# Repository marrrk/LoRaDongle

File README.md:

# LoRaDongle

LoRaDongle is a custom PCB that merges Risc-V with LoRa in a USB Dongle form factor. This repository contains all the project files required to build, utilise and modify the project. Documentation can be read from the site: [https://marrrk.github.io/LoRaDongle/](https://marrrk.github.io/LoRaDongle/)

## Cloning the repository

```bash
git clone --recurse-submodules https://github.com/marrrk/LoRaDongle.git
```

## Directory Structure

- PCB/ -  Contains the Kicad project files, schematics, gerbers, BOM and other PCB related files
- SOC/ - The python scripts that generate, build and load the Risc-V SoC onto the PCB
- firmware/ -  SUpporting firmware that runs on the SoC
- docs/ - Source files for the documentation website

**License** Licensed under [CERN-OHL-P v2](https://cern-ohl.web.cern.ch/) permissive variant or later.

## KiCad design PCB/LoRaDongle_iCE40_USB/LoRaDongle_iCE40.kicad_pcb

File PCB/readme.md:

# Overview
In order to open the Kicad project, open kicad and open the project file `LoRaDongle_iCE40.kicad_pro`. The schematic has been implemented with hierarchal sheets which allows the different submodules to be their own separate schematic. There are five total schematics for each module;
1. LoRaDongle_ice40.kicad_sch
2. power_management.kicad_sch
3. USB_Interface.kicad_sch
4. ice40up5k_sircuit.kicad_sch
5. sx1261_circuitry.kicad_sch

The other files and directories of relevance are:
- libraries/ - kicad symbols and footprints of specific components used
- manufacturing/  - gerbers, assembly files and images for manufacturing
- pdf_schematic/ - pdfs of the schematics of all versions
- silksceen/ - images that are converted into silkscreen footprints

# Contents of the Schematics
## LoRaDongle_ice40
The root schematic that is at the top of the heirarchy. Contains the connecting signals between various subsystems and other components such as the USB connector.

## power_management.kicad_sch
Contains the board's regulator. Steps down 5V to 3.3V and 1.2V.

## USB_Interface.kicad_sch
Houses the FTDI FT2232HL IC that converts the USB protocol into SPI for the FPGA configuration and UART for communicating with the SoC.

## ice40up5k_circuit.kicad_sch
This schematic holds the FPGA banks and related circuitry. This includes the SPI Flash, the oscillator, gas sensor and a header of all unused pins.

## sx1261_circuitry.kicad_sch
This is the RF section of the schematic. It contains the LoRa chip used (SX1261) and the supporting circuitry.

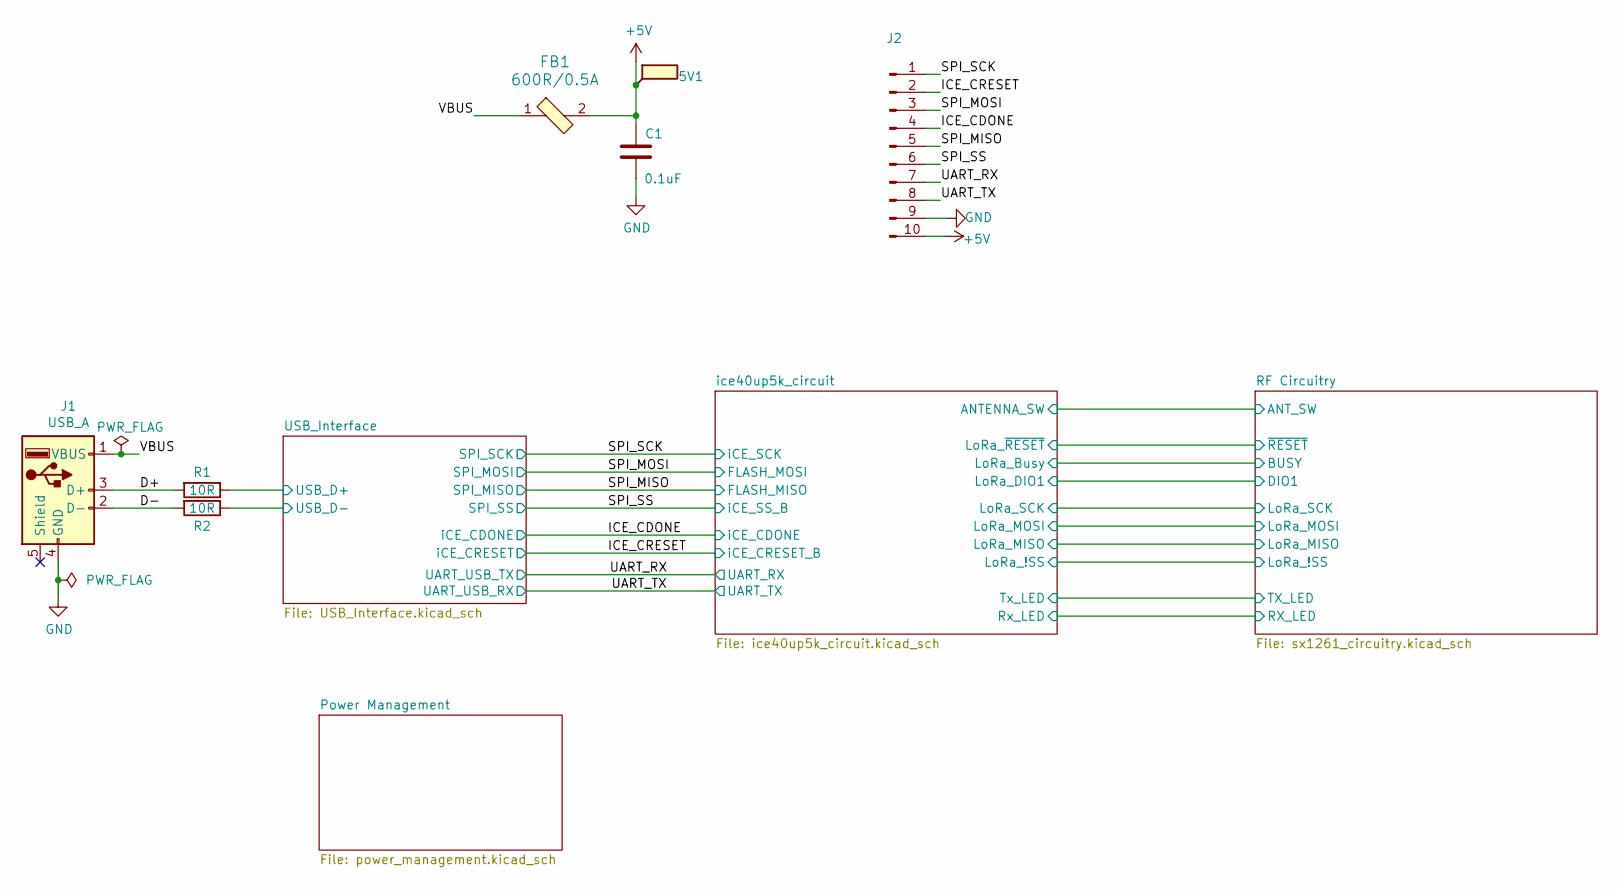
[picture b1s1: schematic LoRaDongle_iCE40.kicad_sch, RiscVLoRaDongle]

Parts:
5V1: 5V; TestPoint_Pad_D2.5mm
C1: 0.1uF; C_0402_1005Metric_Pad0.74x0.62mm_HandSolder; Part Number GCM155R71C104KA55J
FB1: 600R/0.5A; 0603; MPN BLM18AG601SN1D; Digi-Key_PN 490-1014-1-ND
J1: USB_A; USB_A_CNCTech_1001-011-01101_Horizontal; Manufacturer Part Number USB-AP-S-RA-SMT
J2: Conn_01x10_Male; PinHeader_2x05_P2.54mm_Vertical
R1, R2: 10R; R_0402_1005Metric_Pad0.72x0.64mm_HandSolder; Manufacturer Part Number RMCF0402FT10R0

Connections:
+5V: 5V1.1, C1.2, FB1.2, J2.10; also elsewhere on the board
/D+: J1.3 (D+), R1.2
/D-: J1.2 (D-), R2.2
/ICE_CDONE: J2.4; also elsewhere on the board
/ICE_CRESET: J2.2; also elsewhere on the board
/SPI_MISO: J2.5; also elsewhere on the board
/SPI_MOSI: J2.3; also elsewhere on the board
/SPI_SCK: J2.1; also elsewhere on the board
/SPI_SS: J2.6; also elsewhere on the board
/UART_RX: J2.7; also elsewhere on the board
/UART_TX: J2.8; also elsewhere on the board
/USB_Interface/USB_D+: R1.1; also elsewhere on the board
/USB_Interface/USB_D-: R2.1; also elsewhere on the board
/VBUS: FB1.1, J1.1 (VBUS)
GND: C1.1, J1.4 (GND), J2.9; also elsewhere on the board

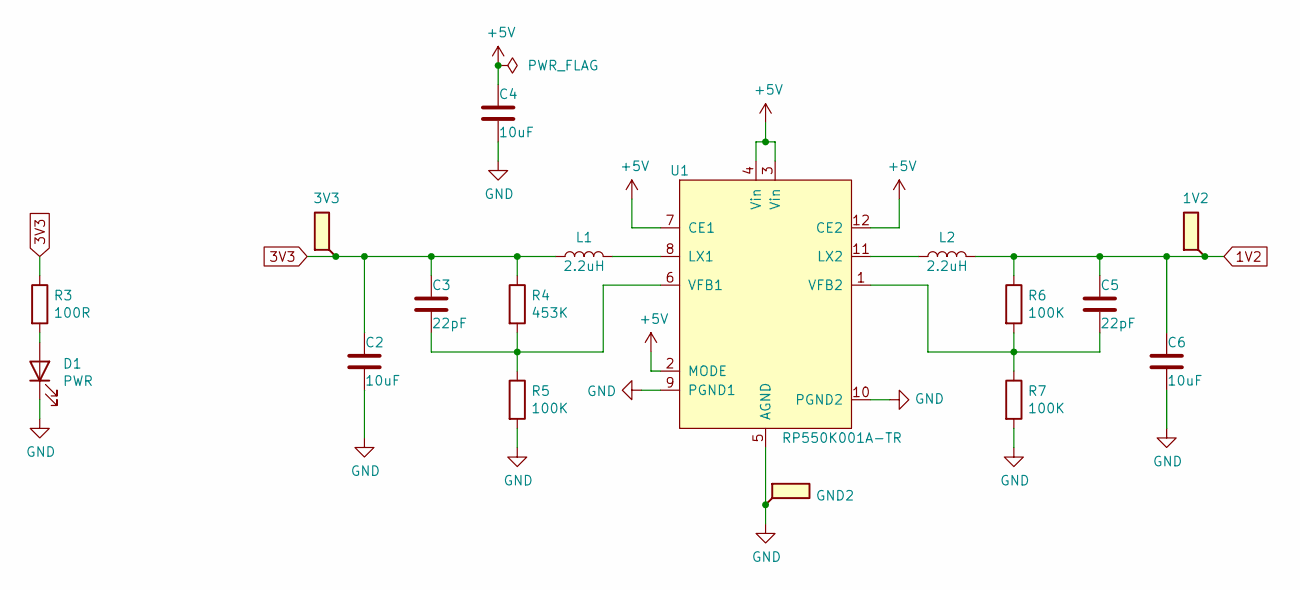
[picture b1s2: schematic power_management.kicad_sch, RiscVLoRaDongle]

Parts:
1V2: 1.2V; TestPoint_Pad_D2.5mm
3V3: 3.3V; TestPoint_Pad_D2.5mm
C2, C4, C6: 10uF; C_0603_1608Metric_Pad1.08x0.95mm_HandSolder; Part Number GRM188R61E106KA73J
C3, C5: 22pF; C_0402_1005Metric_Pad0.74x0.62mm_HandSolder; Part Number GRM1555C1H220FA01D
D1: PWR; LED_0603_1608Metric; Manufacturer Part Number LTST-C191KRKT
GND2: GND; TestPoint_Pad_D2.5mm
L1, L2: 2.2uH; L_0603_1608Metric_Pad1.05x0.95mm_HandSolder; Part Number MCHK1608T2R2MKN
R3: 100R; R_0402_1005Metric_Pad0.72x0.64mm_HandSolder; Manufacturer Part Number RMCF0402FT100R
R4: 453K; R_0402_1005Metric_Pad0.72x0.64mm_HandSolder; Manufacturer Part Number RMCF0402FT453K
R5, R6, R7: 100K; R_0402_1005Metric_Pad0.72x0.64mm_HandSolder; Manufacturer Part Number RMCF0402JT100K
U1: RP550K001A-TR; SON50P270X300X60-13N; Manufacturer Part Number RP550K001A-TR

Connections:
1V2: 1V2.1, C5.2, C6.2, L2.2, R6.1; also elsewhere on the board
3V3: 3V3.1, C2.2, C3.2, L1.1, R3.1, R4.1; also elsewhere on the board
+5V: C4.2, U1.2 (MODE), U1.3 (Vin), U1.4 (Vin), U1.7 (CE1), U1.12 (CE2); also elsewhere on the board
GND: C2.1, C4.1, C6.1, D1.1 (K), GND2.1, R5.2, R7.2, U1.5 (AGND), U1.9 (PGND1), U1.10 (PGND2); also elsewhere on the board
unnamed: C3.1, R4.2, R5.1, U1.6 (VFB1)
unnamed: C5.1, R6.2, R7.1, U1.1 (VFB2)
unnamed: D1.2 (A), R3.2
unnamed: L1.2, U1.8 (LX1)
unnamed: L2.1, U1.11 (LX2)

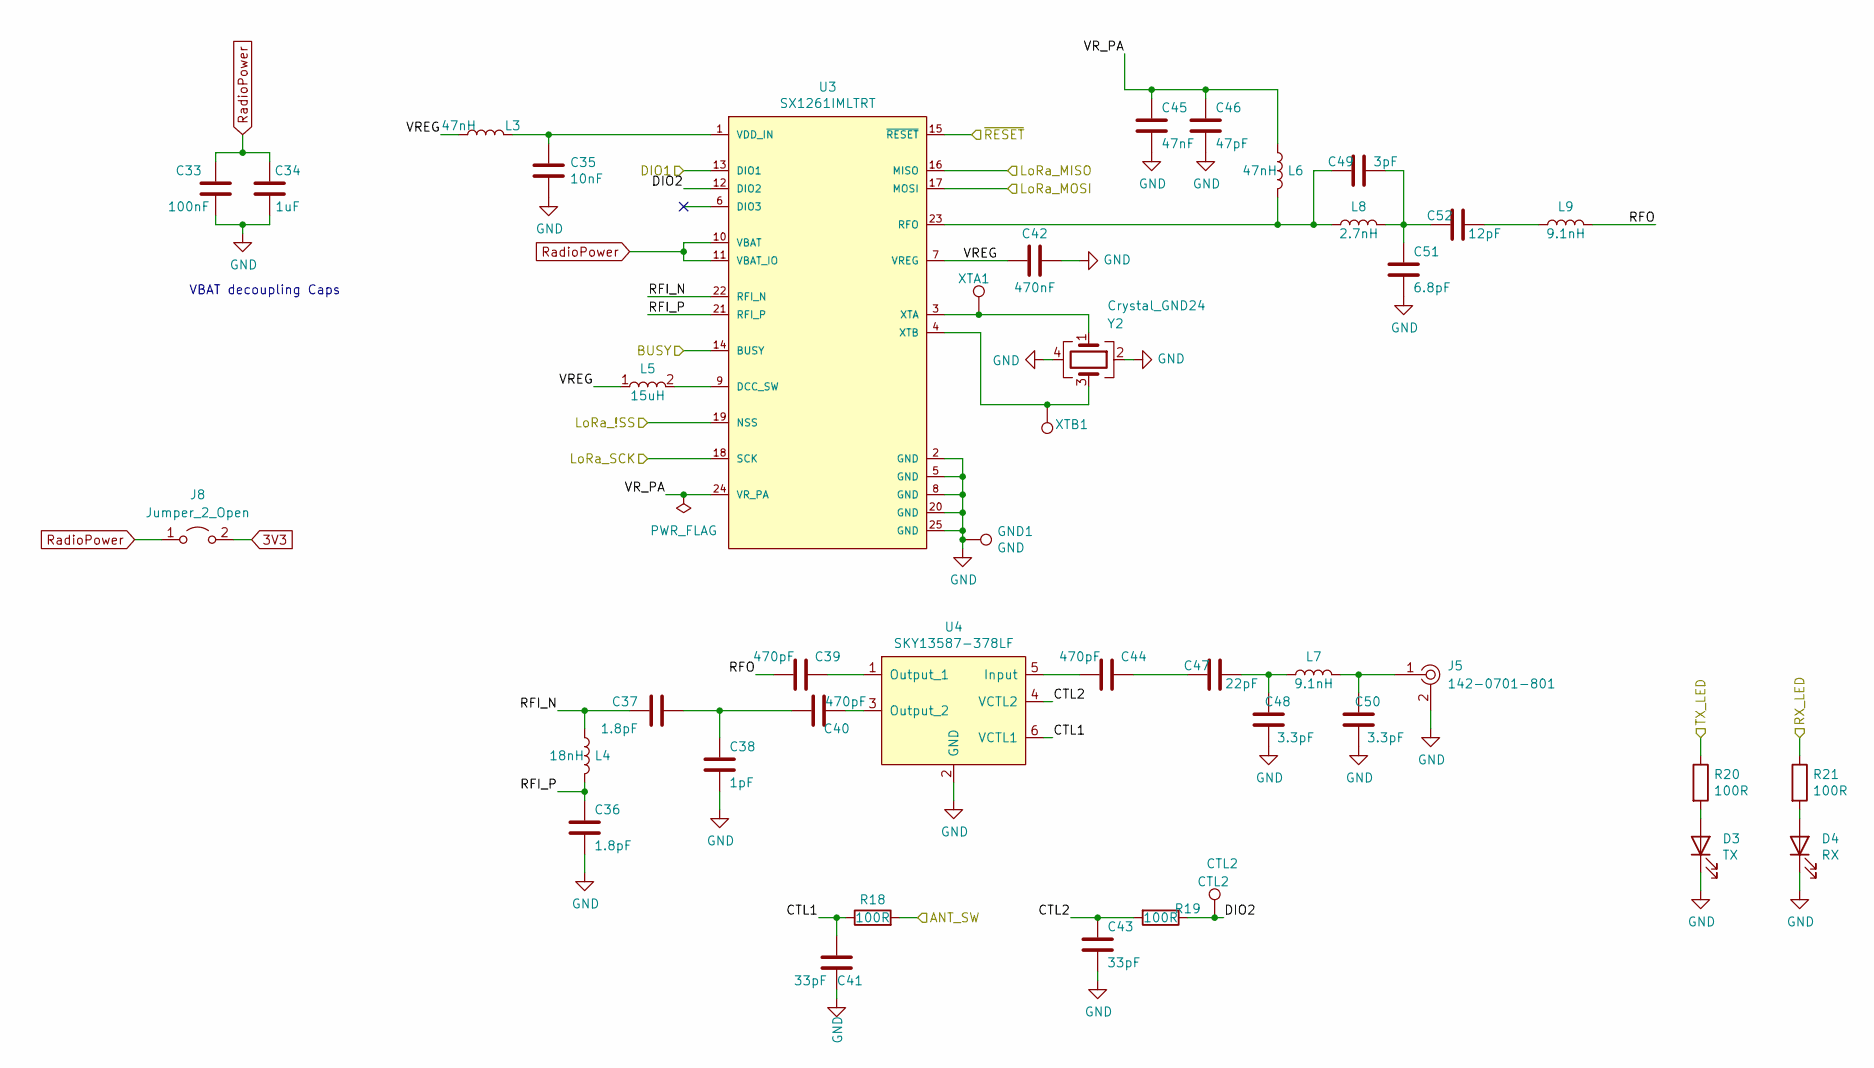
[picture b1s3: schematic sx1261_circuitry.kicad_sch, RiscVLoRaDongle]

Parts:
C33: 100nF; C_0402_1005Metric_Pad0.74x0.62mm_HandSolder; Part Number GRM155R71C104KA88D
C34: 1uF; C_0402_1005Metric_Pad0.74x0.62mm_HandSolder; Manufacturer Part Number GRM155R70J105MA12D
C35: 10nF; C_0402_1005Metric_Pad0.74x0.62mm_HandSolder; Part Number GRM155R71H103KA88J
C36, C37: 1.8pF; C_0402_1005Metric_Pad0.74x0.62mm_HandSolder; part Number GRM1555C1H1R8WA01D
C38: 1pF; C_0402_1005Metric_Pad0.74x0.62mm_HandSolder; part Number GRM1555C1H1R0BA01D
C39, C40, C44: 470pF; C_0402_1005Metric_Pad0.74x0.62mm_HandSolder; Part Number GRM1555C1H471JA01D
C41, C43: 33pF; C_0402_1005Metric_Pad0.74x0.62mm_HandSolder; Part Number CGA2B2C0G1H330J050BA
C42: 470nF; C_0402_1005Metric_Pad0.74x0.62mm_HandSolder; Part Number GRM155R61A474KE15D
C45: 47nF; C_0402_1005Metric_Pad0.74x0.62mm_HandSolder; Part Number GRM155R71C473KA01J
C46: 47pF; C_0402_1005Metric_Pad0.74x0.62mm_HandSolder; Part Number GRM1555C1H470JA01D
C47: 22pF; C_0402_1005Metric_Pad0.74x0.62mm_HandSolder; Part Number GRM1555C1H220JA01D
C48, C50: 3.3pF; C_0402_1005Metric_Pad0.74x0.62mm_HandSolder; Part Number GJM1555C1H3R3DB01D
C49: 3pF; C_0402_1005Metric_Pad0.74x0.62mm_HandSolder; Part Number GRM1555C1H3R0BA01J
C51: 6.8pF; C_0402_1005Metric_Pad0.74x0.62mm_HandSolder; Part Number GRM1555C1H6R8BA01D
C52: 12pF; C_0402_1005Metric_Pad0.74x0.62mm_HandSolder; Part Number GRM1555C1H120JA01J
CTL2: CTL2; TestPoint_Pad_D2.5mm
D3: TX; LED_0603_1608Metric_Pad1.05x0.95mm_HandSolder; Manufacturer Part Number XZVG53W-8
D4: RX; LED_0603_1608Metric_Pad1.05x0.95mm_HandSolder; Manufacturer Part Number XZVG53W-8
GND1: GND; TestPoint_Pad_D2.5mm
J5: 142-0701-801; RF_SMA_BoardEdge_142-0701-801; MPN 142-0701-801; Digi-Key_PN J502-ND
J8: Jumper_2_Open; PinHeader_1x02_P2.54mm_Vertical
L3: 47nH; L_0402_1005Metric_Pad0.77x0.64mm_HandSolder; PartNumber LQW15AN47NJ00D
L4: 18nH; L_0402_1005Metric_Pad0.77x0.64mm_HandSolder; part Number LQW15AN18NH00D
L5: 15uH; VLS2016; Manufacturer_Part_Number VLS201610CX-150M-1; Mouser Part Number 810-VLS201610CX150M1
L6: 47nH; L_0402_1005Metric_Pad0.77x0.64mm_HandSolder; Part Number LQW15AN47NJ00D
L7, L9: 9.1nH; L_0402_1005Metric_Pad0.77x0.64mm_HandSolder; Part Number LQW15AN9N1H00D
L8: 2.7nH; L_0402_1005Metric_Pad0.77x0.64mm_HandSolder; Part Number LQW15AN2N7C00D
R18, R19, R20, R21: 100R; R_0402_1005Metric_Pad0.72x0.64mm_HandSolder; Manufacturer Part Number RMCF0402FT100R
U3: SX1261IMLTRT; Semtech-QFN24-0-0-0; mouser part number 947-SX1261IMLTRT; digikey description TXRX LORA SUB-GHZ 15DBM 24MLPQ
U4: SKY13587-378LF; SW_SKYA21012; Manufacturer Part Number SKY13587-378LF
XTA1: XTA; TestPoint_Pad_D2.5mm
XTB1: XTB; TestPoint_Pad_D2.5mm
Y2: Crystal_GND24; Crystal_SMD_2520-4Pin_2.5x2.0mm; Part Number ECS-320-10-36B-CKM-TR

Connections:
3V3: J8.2 (B); also elsewhere on the board
/RF Circuitry/ANT_SW: R18.2; also elsewhere on the board
/RF Circuitry/BUSY: U3.14 (BUSY); also elsewhere on the board
/RF Circuitry/CTL1: C41.2, R18.1, U4.6 (VCTL1)
/RF Circuitry/CTL2: C43.1, R19.2, U4.4 (VCTL2)
/RF Circuitry/DIO1: U3.13 (DIO1); also elsewhere on the board
/RF Circuitry/DIO2: CTL2.1, R19.1, U3.12 (DIO2)
/RF Circuitry/LoRa_!SS: U3.19 (NSS); also elsewhere on the board
/RF Circuitry/LoRa_MISO: U3.16 (MISO); also elsewhere on the board
/RF Circuitry/LoRa_MOSI: U3.17 (MOSI); also elsewhere on the board
/RF Circuitry/LoRa_SCK: U3.18 (SCK); also elsewhere on the board
/RF Circuitry/RFI_N: C37.1, L4.1, U3.22 (RFI_N)
/RF Circuitry/RFI_P: C36.1, L4.2, U3.21 (RFI_P)
/RF Circuitry/RFO: C39.1, L9.2
/RF Circuitry/RX_LED: R21.1; also elsewhere on the board
/RF Circuitry/TX_LED: R20.1; also elsewhere on the board
/RF Circuitry/VREG: C42.2, L3.1, L5.1, U3.7 (VREG)
/RF Circuitry/VR_PA: C45.1, C46.1, L6.1, U3.24 (VR_PA)
/RF Circuitry/~RESET: U3.15 (~RESET); also elsewhere on the board
GND: C33.1, C34.1, C35.2, C36.2, C38.2, C41.1, C42.1, C43.2, C45.2, C46.2, C48.1, C50.1, C51.2, D3.1 (K), D4.1 (K), GND1.1, J5.2, U3.2 (GND), U3.5 (GND), U3.8 (GND), U3.20 (GND), U3.25 (GND), U4.2 (GND), Y2.2, Y2.4; also elsewhere on the board
unnamed: C35.1, L3.2, U3.1 (VDD_IN)
unnamed: C37.2, C38.1, C40.1
unnamed: C39.2, U4.1 (Output_1)
unnamed: C40.2, U4.3 (Output_2)
unnamed: C44.1, U4.5 (Input)
unnamed: C44.2, C47.2
unnamed: C47.1, C48.2, L7.1
unnamed: C49.1, C51.1, C52.2, L8.2
unnamed: C49.2, L6.2, L8.1, U3.23 (RFO)
unnamed: C50.2, J5.1, L7.2
unnamed: C52.1, L9.1
unnamed: D3.2 (A), R20.2
unnamed: D4.2 (A), R21.2
unnamed: L5.2, U3.9 (DCC_SW)
unnamed: U3.3 (XTA), XTA1.1, Y2.1
unnamed: U3.4 (XTB), XTB1.1, Y2.3
RadioPower: C33.2, C34.2, J8.1 (A), U3.10 (VBAT), U3.11 (VBAT_IO)

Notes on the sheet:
VBAT decoupling Caps

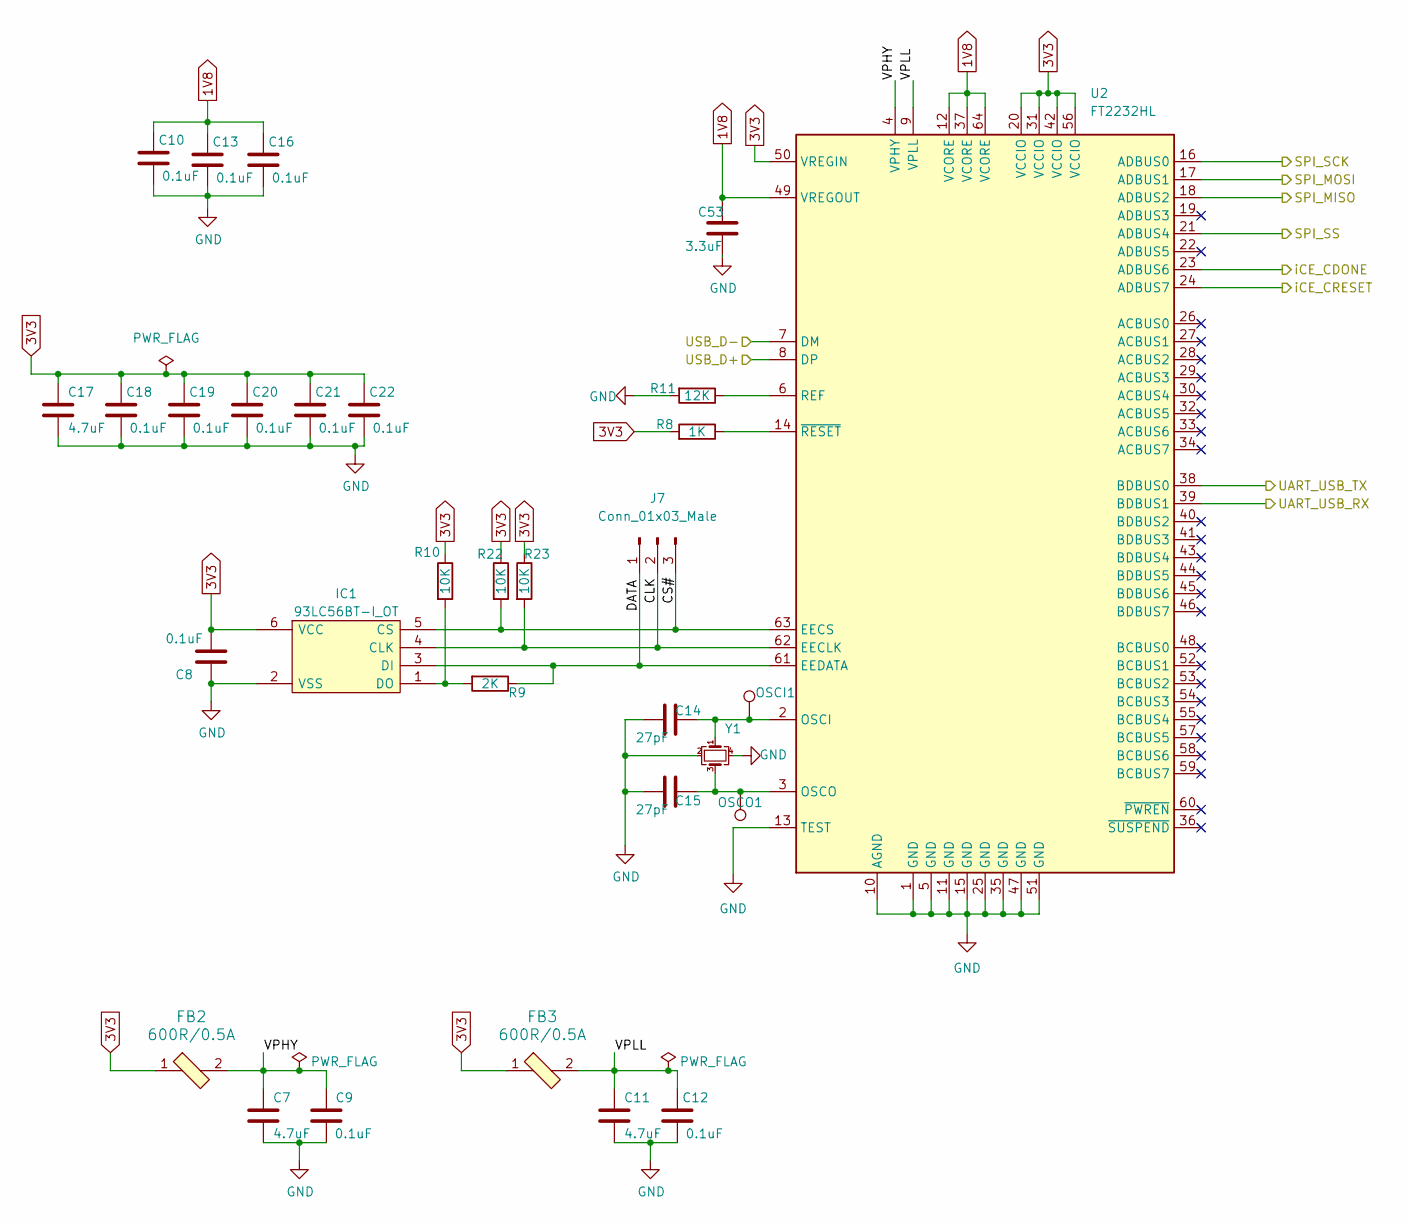
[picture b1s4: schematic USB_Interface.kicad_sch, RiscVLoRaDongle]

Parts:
C7, C11, C17: 4.7uF; C_0402_1005Metric_Pad0.74x0.62mm_HandSolder; Part Number GRM155C80J475MEAAD
C8, C9, C10, C12, C13, C16, C18, C19, C20, C21, C22: 0.1uF; C_0402_1005Metric_Pad0.74x0.62mm_HandSolder; Part Number GCM155R71C104KA55J
C14, C15: 27pF; C_0603_1608Metric_Pad1.08x0.95mm_HandSolder; Manufacturer Part Number GRM1885C1H270JA01D
C53: 3.3uF; C_0603_1608Metric_Pad1.08x0.95mm_HandSolder; Manufacturer Part Number CL10A335KP8NNNC
FB2, FB3: 600R/0.5A; 0603; MPN BLM18AG601SN1D; Digi-Key_PN 490-1014-1-ND
IC1: 93LC56BT-I_OT; SOT95P270X145-6N; Manufacturer_Part_Number 93LC56BT-I/OT; Mouser Part Number 579-93LC56BT-I/OT
J7: Conn_01x03_Male; PinHeader_1x03_P2.54mm_Vertical
OSCI1: OSCI; TestPoint_Pad_D2.5mm
OSCO1: OSCO; TestPoint_Pad_D2.5mm
R8: 1K; R_0402_1005Metric_Pad0.72x0.64mm_HandSolder; Manufacturer Part Number RMCF0402FT1K00
R9: 2K; R_0402_1005Metric_Pad0.72x0.64mm_HandSolder; Manufacturer Part Number RMCF0402FT2K00
R10, R22, R23: 10K; R_0402_1005Metric_Pad0.72x0.64mm_HandSolder; Manufacturer Part Number RMCF0402FT10K0
R11: 12K; R_0402_1005Metric_Pad0.72x0.64mm_HandSolder; Manufacturer Part Number RMCF0402FT12K0
U2: FT2232HL; LQFP-64_10x10mm_P0.5mm; Manufacturer Part Number FT2232HL
Y1: Crystal_GND24_Small; Crystal_SMD_3225-4Pin_3.2x2.5mm; Part Number ABM8-12.000MHZ-B2-T

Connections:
1V8: C10.2, C13.2, C16.2, C53.1, U2.12 (VCORE), U2.37 (VCORE), U2.49 (VREGOUT), U2.64 (VCORE)
3V3: C8.2, C17.1, C18.2, C19.2, C20.2, C21.2, C22.2, FB2.1, FB3.1, IC1.6 (VCC), R8.2, R10.1, R22.1, R23.1, U2.20 (VCCIO), U2.31 (VCCIO), U2.42 (VCCIO), U2.50 (VREGIN), U2.56 (VCCIO); also elsewhere on the board
/ICE_CDONE: U2.23 (ADBUS6); also elsewhere on the board
/ICE_CRESET: U2.24 (ADBUS7); also elsewhere on the board
/SPI_MISO: U2.18 (ADBUS2); also elsewhere on the board
/SPI_MOSI: U2.17 (ADBUS1); also elsewhere on the board
/SPI_SCK: U2.16 (ADBUS0); also elsewhere on the board
/SPI_SS: U2.21 (ADBUS4); also elsewhere on the board
/UART_RX: U2.38 (BDBUS0); also elsewhere on the board
/UART_TX: U2.39 (BDBUS1); also elsewhere on the board
/USB_Interface/CLK: IC1.4 (CLK), J7.2, R23.2, U2.62 (EECLK)
/USB_Interface/CS#: IC1.5 (CS), J7.3, R22.2, U2.63 (EECS)
/USB_Interface/DATA: IC1.3 (DI), J7.1, R9.1, U2.61 (EEDATA)
/USB_Interface/USB_D+: U2.8 (DP); also elsewhere on the board
/USB_Interface/USB_D-: U2.7 (DM); also elsewhere on the board
/USB_Interface/VPHY: C7.1, C9.2, FB2.2, U2.4 (VPHY)
/USB_Interface/VPLL: C11.1, C12.2, FB3.2, U2.9 (VPLL)
GND: C7.2, C8.1, C9.1, C10.1, C11.2, C12.1, C13.1, C14.2, C15.2, C16.1, C17.2, C18.1, C19.1, C20.1, C21.1, C22.1, C53.2, IC1.2 (VSS), R11.2, U2.1 (GND), U2.5 (GND), U2.10 (AGND), U2.11 (GND), U2.13 (TEST), U2.15 (GND), U2.25 (GND), U2.35 (GND), U2.47 (GND), U2.51 (GND), Y1.2, Y1.4; also elsewhere on the board
unnamed: C14.1, OSCI1.1, U2.2 (OSCI), Y1.1
unnamed: C15.1, OSCO1.1, U2.3 (OSCO), Y1.3
unnamed: IC1.1 (DO), R9.2, R10.2
unnamed: R8.1, U2.14 (~RESET)
unnamed: R11.1, U2.6 (REF)

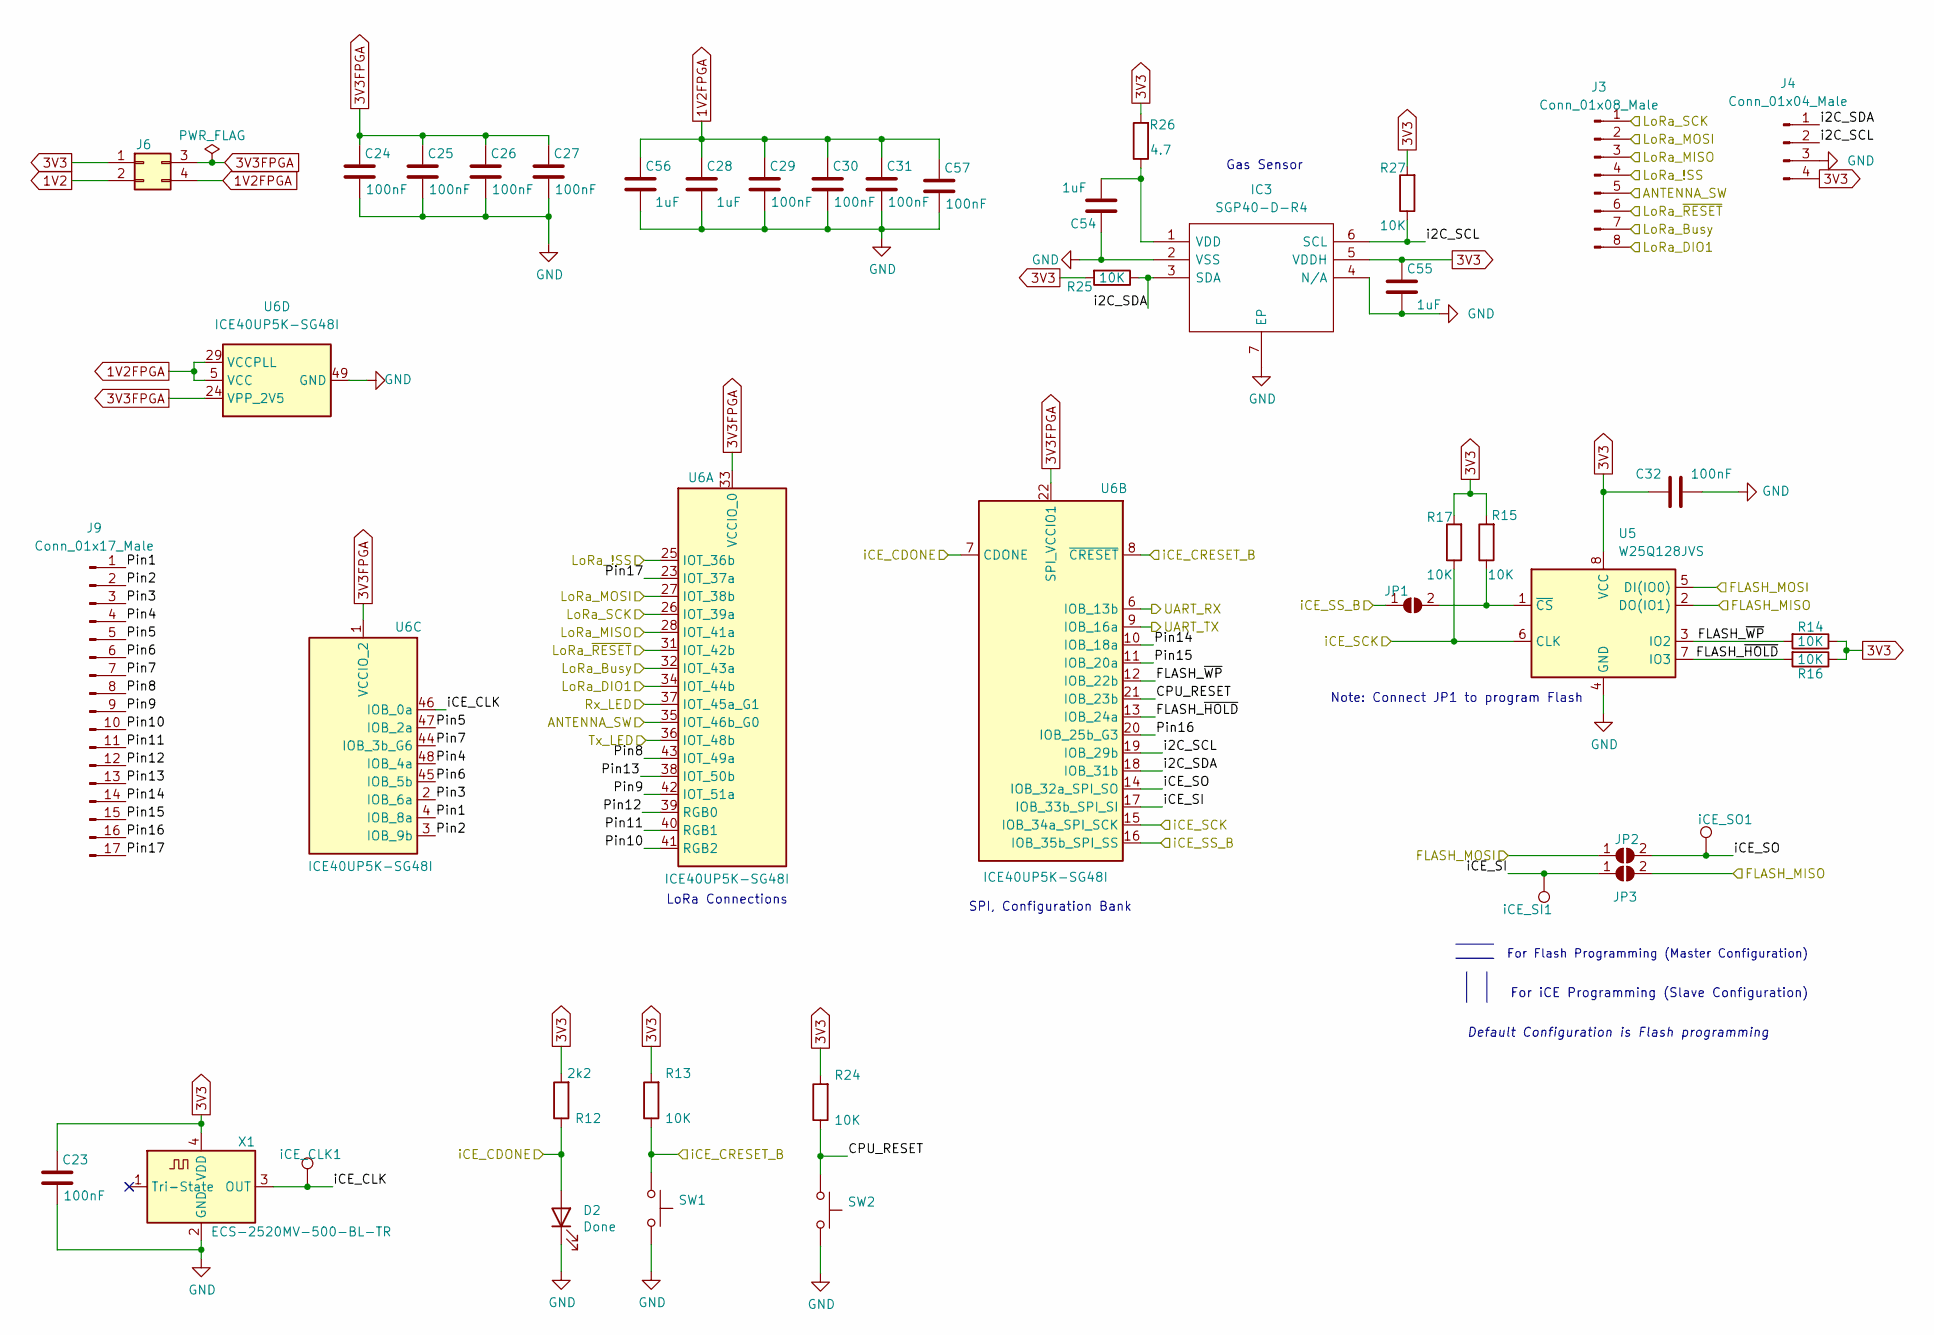
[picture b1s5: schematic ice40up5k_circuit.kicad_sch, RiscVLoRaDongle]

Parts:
C23, C24, C25, C26, C27, C29, C30, C31, C32, C57: 100nF; C_0402_1005Metric_Pad0.74x0.62mm_HandSolder; Part Number GRM155R71C104KA88D
C28, C54, C55, C56: 1uF; C_0402_1005Metric_Pad0.74x0.62mm_HandSolder; Part Number GRM155R70J105MA12D
D2: Done; LED_0603_1608Metric_Pad1.05x0.95mm_HandSolder; Manufacturer Part Number XZCBD53W-1
IC3: SGP40-D-R4; SON80P244X244X95-7N; Manufacturer_Part_Number SGP40-D-R4; Mouser Part Number 403-SGP40-D-R4
J3: Conn_01x08_Male; PinHeader_2x04_P2.54mm_Vertical
J4: Conn_01x04_Male; PinHeader_1x04_P2.54mm_Vertical
J6: Conn_02x02_Top_Bottom; PinHeader_2x02_P2.54mm_Vertical
J9: Conn_01x17_Male; PinHeader_1x17_P2.54mm_Vertical
JP1, JP2, JP3: SolderJumper_2_Open; R_0603_1608Metric_Pad0.98x0.95mm_HandSolder; Manufacturer Part Number RMCF0603ZT0R00
R12: 2k2; R_0402_1005Metric_Pad0.72x0.64mm_HandSolder; Manufacturer Part Number RC0402FR-072K2L
R13, R14, R15, R16, R17, R24, R25, R27: 10K; R_0402_1005Metric_Pad0.72x0.64mm_HandSolder; Manufacturer Part Number RMCF0402FT10K0
R26: 4.7; R_0402_1005Metric_Pad0.72x0.64mm_HandSolder; Manufacturer Part Number RMCF0402FT4R70
SW1, SW2: SW_Push; SW_PUSH_6mm_H5mm; Manufacturer Part Number TS02-66-55-BK-100-LCR-D
U5: W25Q128JVS; SOIC-8_5.23x5.23mm_P1.27mm; Manufacturer Part Number W25Q128JVSIM TR
U6: ICE40UP5K-SG48I; QFN-48-1EP_7x7mm_P0.5mm_EP5.6x5.6mm; Manufacturer Part Number ICE40UP5K-SG48IT
X1: ECS-2520MV-500-BL-TR; Oscillator_SMD_ECS_2520MV-xxx-xx-4Pin_2.5x2.0mm; Manufacturer Part Number ECS-2520MV-500-BL-TR
iCE_CLK1: iCE_CLK; TestPoint_Pad_D2.5mm
iCE_SI1: iCE_SI; TestPoint_Pad_D2.5mm
iCE_SO1: iCE_SO; TestPoint_Pad_D2.5mm

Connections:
1V2: J6.2; also elsewhere on the board
1V2FPGA: C28.2, C29.2, C30.2, C31.2, C56.2, C57.2, J6.4, U6.5 (VCC), U6.29 (VCCPLL), U6.30 (VCC)
3V3: C23.2, C32.2, C55.2, IC3.5 (VDDH), J4.4, J6.1, R12.2, R13.2, R14.1, R15.2, R16.1, R17.2, R24.2, R25.2, R26.2, R27.2, U5.8 (VCC), X1.4 (VDD); also elsewhere on the board
3V3FPGA: C24.2, C25.2, C26.2, C27.2, J6.3, U6.1 (VCCIO_2), U6.22 (SPI_VCCIO1), U6.24 (VPP_2V5), U6.33 (VCCIO_0)
/ICE_CDONE: D2.2 (A), R12.1, U6.7 (CDONE); also elsewhere on the board
/ICE_CRESET: R13.1, SW1.1, U6.8 (~CRESET); also elsewhere on the board
/RF Circuitry/ANT_SW: J3.5, U6.35 (IOT_46b_G0); also elsewhere on the board
/RF Circuitry/BUSY: J3.7, U6.32 (IOT_43a); also elsewhere on the board
/RF Circuitry/DIO1: J3.8, U6.34 (IOT_44b); also elsewhere on the board
/RF Circuitry/LoRa_!SS: J3.4, U6.25 (IOT_36b); also elsewhere on the board
/RF Circuitry/LoRa_MISO: J3.3, U6.28 (IOT_41a); also elsewhere on the board
/RF Circuitry/LoRa_MOSI: J3.2, U6.27 (IOT_38b); also elsewhere on the board
/RF Circuitry/LoRa_SCK: J3.1, U6.26 (IOT_39a); also elsewhere on the board
/RF Circuitry/RX_LED: U6.37 (IOT_45a_G1); also elsewhere on the board
/RF Circuitry/TX_LED: U6.36 (IOT_48b); also elsewhere on the board
/RF Circuitry/~RESET: J3.6, U6.31 (IOT_42b); also elsewhere on the board
/SPI_MISO: JP3.2 (B), U5.2 (DO(IO1)); also elsewhere on the board
/SPI_MOSI: JP2.1 (A), U5.5 (DI(IO0)); also elsewhere on the board
/SPI_SCK: R17.1, U5.6 (CLK), U6.15 (IOB_34a_SPI_SCK); also elsewhere on the board
/SPI_SS: JP1.1 (A), U6.16 (IOB_35b_SPI_SS); also elsewhere on the board
/UART_RX: U6.6 (IOB_13b); also elsewhere on the board
/UART_TX: U6.9 (IOB_16a); also elsewhere on the board
/ice40up5k_circuit/CPU_RESET: R24.1, SW2.1, U6.21 (IOB_23b)
/ice40up5k_circuit/FLASH_~HOLD: R16.2, U5.7 (IO3), U6.13 (IOB_24a)
/ice40up5k_circuit/FLASH_~WP: R14.2, U5.3 (IO2), U6.12 (IOB_22b)
/ice40up5k_circuit/Pin1: J9.1, U6.4 (IOB_8a)
/ice40up5k_circuit/Pin2: J9.2, U6.3 (IOB_9b)
/ice40up5k_circuit/Pin3: J9.3, U6.2 (IOB_6a)
/ice40up5k_circuit/Pin4: J9.4, U6.48 (IOB_4a)
/ice40up5k_circuit/Pin5: J9.5, U6.47 (IOB_2a)
/ice40up5k_circuit/Pin6: J9.6, U6.45 (IOB_5b)
/ice40up5k_circuit/Pin7: J9.7, U6.44 (IOB_3b_G6)
/ice40up5k_circuit/Pin8: J9.8, U6.43 (IOT_49a)
/ice40up5k_circuit/Pin9: J9.9, U6.42 (IOT_51a)
/ice40up5k_circuit/Pin10: J9.10, U6.41 (RGB2)
/ice40up5k_circuit/Pin11: J9.11, U6.40 (RGB1)
/ice40up5k_circuit/Pin12: J9.12, U6.39 (RGB0)
/ice40up5k_circuit/Pin13: J9.13, U6.38 (IOT_50b)
/ice40up5k_circuit/Pin14: J9.14, U6.10 (IOB_18a)
/ice40up5k_circuit/Pin15: J9.15, U6.11 (IOB_20a)
/ice40up5k_circuit/Pin16: J9.16, U6.20 (IOB_25b_G3)
/ice40up5k_circuit/Pin17: J9.17, U6.23 (IOT_37a)
/ice40up5k_circuit/i2C_SCL: IC3.6 (SCL), J4.2, R27.1, U6.19 (IOB_29b)
/ice40up5k_circuit/i2C_SDA: IC3.3 (SDA), J4.1, R25.1, U6.18 (IOB_31b)
/ice40up5k_circuit/iCE_CLK: U6.46 (IOB_0a), X1.3 (OUT), iCE_CLK1.1
/ice40up5k_circuit/iCE_SI: JP3.1 (A), U6.17 (IOB_33b_SPI_SI), iCE_SI1.1
/ice40up5k_circuit/iCE_SO: JP2.2 (B), U6.14 (IOB_32a_SPI_SO), iCE_SO1.1
GND: C23.1, C24.1, C25.1, C26.1, C27.1, C28.1, C29.1, C30.1, C31.1, C32.1, C54.2, C55.1, C56.1, C57.1, D2.1 (K), IC3.2 (VSS), IC3.4 (N/A), IC3.7 (EP), J4.3, SW1.2, SW2.2, U5.4 (GND), U6.49 (GND), X1.2 (GND); also elsewhere on the board
unnamed: C54.1, IC3.1 (VDD), R26.1
unnamed: JP1.2 (B), R15.1, U5.1 (~CS)

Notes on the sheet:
LoRa Connections
Gas Sensor
SPI, Configuration Bank
Note: Connect JP1 to program Flash
For Flash Programming (Master Configuration)
Default Configuration is Flash programming
For iCE Programming (Slave Configuration)
